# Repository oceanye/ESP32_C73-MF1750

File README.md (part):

# ESP32-S3 + E2802 Cascade eInk 调试工程

## 当前现场与开发状态（2026-08-08）

> 本节只作快速入口；任何后续变化、数量、测试批次和文件哈希均以
> [`docs/STATUS_HANDOFF.md`](docs/STATUS_HANDOFF.md) 为唯一事实源。

- 驱动板/J2 电源已关闭，ESP32 单独保持供电；当前未消费的可见刷新授权为 `0`，没有
  设备访问、刷写或面板动作在进行。
- RC2G 的 N0/N1 已放行真屏 action 为 `4/4`，均已闭环；对应 fixed claims 已永久消费，
  不得重跑。
- N2--N8 的 physical production-live 软件入口、深绑定、单次执行/finalizer/analyzer 均已落地，
  软件闭环为 `7/7`；对应旧 UNBOUND/self-sealed/legacy public live 入口在 claim/联网前
  fail closed。真屏阶段仍只有 N0/N1 完成；最终状态必须读取 STATUS。
- 各阶段的实际 process-policy/供应商限额、每 action 最新 usage/profile review、测量资产和授权
  尚未形成。软件入口
  就绪不等于硬件放行；reviewed limit/runtime、仪器、供应商数据、panel/build/
  prior 绑定和逐 action 授权等外部门禁仍阻断对应真屏任务；晚间顺序见
  [`docs/MF1750_N2_N8_EVENING_TASK_BOARD_2026-08-08.md`](docs/MF1750_N2_N8_EVENING_TASK_BOARD_2026-08-08.md)。

## 当前交接入口

- **唯一当前状态页（完成数、剩余数、目的、下一步）：[`docs/STATUS_HANDOFF.md`](docs/STATUS_HANDOFF.md)**
- **N2--N8 晚间逐项真屏任务板：[`docs/MF1750_N2_N8_EVENING_TASK_BOARD_2026-08-08.md`](docs/MF1750_N2_N8_EVENING_TASK_BOARD_2026-08-08.md)**
- 阶段一制造与固件交接：[`docs/STAGE1_REV_A1_HANDOFF_2026-07-13.md`](docs/STAGE1_REV_A1_HANDOFF_2026-07-13.md)
- 阶段二 ESP32/电池整合设计输入：[`docs/STAGE2_ESP32_BATTERY_INTEGRATION_BRIEF.md`](docs/STAGE2_ESP32_BATTERY_INTEGRATION_BRIEF.md)
- Rev B-mini ESP32/TF/电源与器件初评：[`docs/H1_REV_B_MINI_COMPONENT_ASSESSMENT_2026-08-05.md`](docs/H1_REV_B_MINI_COMPONENT_ASSESSMENT_2026-08-05.md)
- Rev B-mini L1/L2 小型化详细评估：[`docs/REV_B_MINI_L1_L2_DOWNSIZING_ASSESSMENT_2026-08-05.md`](docs/REV_B_MINI_L1_L2_DOWNSIZING_ASSESSMENT_2026-08-05.md)
- Rev A1 R16 级联整屏实测：[`docs/REV_A1_R16_CASCADE_FULLFRAME_TEST_2026-08-04.md`](docs/REV_A1_R16_CASCADE_FULLFRAME_TEST_2026-08-04.md)
- 基础驱动与 API 参考：[`docs/MF1750_DRIVER_API.md`](docs/MF1750_DRIVER_API.md)
- H0 Rev A1/RC2C 归档状态：[`docs/H0_REV_A1_RC2C_ARCHIVE_STATUS_2026-08-06.md`](docs/H0_REV_A1_RC2C_ARCHIVE_STATUS_2026-08-06.md)
- RC2F/C4/C2 分阶段上机任务包：[`docs/RC2F_C4_C2_HARDWARE_VALIDATION_TASKS_2026-08-06.md`](docs/RC2F_C4_C2_HARDWARE_VALIDATION_TASKS_2026-08-06.md)
- Spectra 6 色域映射高级 AI Handoff：[`docs/G1_SPECTRA6_GAMUT_MAPPING_HANDOFF_2026-08-05.md`](docs/G1_SPECTRA6_GAMUT_MAPPING_HANDOFF_2026-08-05.md)
- 重叠感知空间半色调研究：[`docs/S1_OVERLAP_AWARE_HALFTONE_RESEARCH_2026-08-06.md`](docs/S1_OVERLAP_AWARE_HALFTONE_RESEARCH_2026-08-06.md)
- G1/S1 混色与显示器模拟交接：[`docs/G1_S1_MONITOR_SIMULATION_HANDOFF_2026-08-06.md`](docs/G1_S1_MONITOR_SIMULATION_HANDOFF_2026-08-06.md)
- G1/S1 晚些真屏验证任务：[`docs/G1_S1_REAL_PANEL_VALIDATION_TASKS_2026-08-06.md`](docs/G1_S1_REAL_PANEL_VALIDATION_TASKS_2026-08-06.md)
- RC2G 白天开发与晚间逐项真屏 Campaign：[`docs/MF1750_RC2G_EVENING_HARDWARE_CAMPAIGN_2026-08-07.md`](docs/MF1750_RC2G_EVENING_HARDWARE_CAMPAIGN_2026-08-07.md)
- 网络照片与随机刷新 TODO：[`docs/TODO_NETWORK_RANDOM_PHOTO_PIPELINE.md`](docs/TODO_NETWORK_RANDOM_PHOTO_PIPELINE.md)
- 扩展颜色/亮度技术可行性结论：[`docs/EPD_EXTENDED_COLOR_FEASIBILITY_2026-08-05.md`](docs/EPD_EXTENDED_COLOR_FEASIBILITY_2026-08-05.md)
- 扩展颜色/亮度后续测试 TODO：[`docs/TODO_EPD_EXTENDED_COLOR_TESTS_2026-08-05.md`](docs/TODO_EPD_EXTENDED_COLOR_TESTS_2026-08-05.md)
- C3 转移感知优化器离线交接：[`docs/C3_TRANSITION_OPTIMIZER_OFFLINE_HANDOFF_2026-08-08.md`](docs/C3_TRANSITION_OPTIMIZER_OFFLINE_HANDOFF_2026-08-08.md)
- 扩展颜色远端成果集成审查：[`docs/EXTENDED_COLOR_INTEGRATION_REVIEW_2026-08-05.md`](docs/EXTENDED_COLOR_INTEGRATION_REVIEW_2026-08-05.md)
- 主机快速刷新、CI 与六色流水线总集成：[`docs/HOST_REFRESH_COLOR_INTEGRATION_2026-08-04.md`](docs/HOST_REFRESH_COLOR_INTEGRATION_2026-08-04.md)
- 多 AI TODO 与 Git 集成计划：[`docs/TODO_MULTI_AI_HANDOFF_PLAN_2026-08-04.md`](docs/TODO_MULTI_AI_HANDOFF_PLAN_2026-08-04.md)
- 新对话启动提示：[`docs/NEXT_SESSION_PROMPT.md`](docs/NEXT_SESSION_PROMPT.md)
- 1210 电容焊盘复核：[`docs/REV_A1_1210_PAD_AUDIT.md`](docs/REV_A1_1210_PAD_AUDIT.md)
- Rev A1 最终生产检查：[`hardware/mf1750_production_v1/production/FINAL_PREFLIGHT_revA1.md`](hardware/mf1750_production_v1/production/FINAL_PREFLIGHT_revA1.md)

当前状态：`MF1750 REV A1` 已完成加工与基础驱动 D0 实机验收。生产冻结文件
仍为带 `revA1_Q1FIX` 名称的 Gerber、BOM、CPL，禁止重新生成或覆盖。
H0 已生成基于 Git 对象的源码/证据归档和 SHA-256 清单，但精确验收二进制仍缺失，
且尚未完成异机持久副本；硬件验收 tag 未获明确授权，不能宣称 H0 已最终封版。

## 历史累计结论（起于 2026-08-04；不作为当前状态入口）

> 本节保留已经发生的硬件与软件证据，段内的“当前”“下一步”和回归计数只代表各自记录
> 时点；与顶部摘要或 STATUS 冲突时，一律以 STATUS 为准。

- 当前硬件为 R15 拆除、R16 0 Ω 安装、GPIO10 独立控制 `SL_CSB`。
- 两颗 SPD1657B 的 revision 均稳定读为 `0x04`。
- 向两颗控制器分别写 `CCSET(0xE0)=0x01` 后，左右半屏可独立显示纯色，
  并已实测完整 1024x600 连续六色色条。
- 从左到右白/黑/红/黄/蓝/绿正确，中央红/黄中缝清晰；正式分帧为每行
  512 字节，CS1 取前 256 字节、CS2 取后 256 字节。
- ESP32-S3 已由 esptool 与运行时共同确认约 8 MB OPI PSRAM；307200 字节
  规范帧的主机、设备生成器和非刷新 ingress 哈希均已通过。
- 当前源码候选固件为
  `MF1750_DRIVER_RC2G_R16_CCSET_MAPHASH_COLORGUARD_JOBTRACE_PSRFIX_WEBPHOTO_PHYSICAL_BUSYEDGE_2026-08-07`
  / driver API V3；它在 RC2F 上增加 PON/DRF/POF 命令前 idle、新 BUSY 边沿和
  safe-finish/final GPIO 证据。build 为 815664 字节、SHA-256 `9DF897…0CD772`，已于
  2026-08-07 精确刷入；MAP job1 与 macro4 job2 的协议、nominal timing、电气和
  frame fidelity 均通过。该 exact-action 范围不自动继承为其他算法资格。
  HTTP ingress 与公开驱动 API 都会在任何面板 I/O 前拒绝
  `0x4/0x7..0xF` 非法像素码；PON/DRF/POF 未观察到 BUSY 会 fail closed，
  POF 后的 PSR 寄存器写入保留等待证据但不要求额外 BUSY assertion；诊断报告
  以匹配的 operation ID 与产生它的 job/build 绑定。
- RC2C/V3 已用同一 MAP_ORIENT_V1 完成 100 kHz 协议复验和正式 1 MHz
  `/api/frame` 实屏验收；方向、中缝、颜色、完整/双 DTM 哈希、PON/DRF/POF
  BUSY、电源、温度及断电安全状态均正确。1 MHz 总耗时 34.187 秒，其中两半
  DTM 上传各 2.444 秒、DRF 约 21.7 秒。
- 主机 PSRAM 预检修正点 `2b19f75` 的 203 项回归、repository contract、
  PlatformIO build 与 GitHub CI run `30917129233` 全部通过；验收记录提交
  `fd548e3` 的 CI run `30918209821` 也通过。RC2C 实测 `firmware.bin` 为
  796272 字节、SHA-256 `F763FE…F45C475B`；RC2D 为 803120 字节、SHA-256
  `AE7427…943DAD`，
  在重新实屏验收前不得与 RC2C 的硬件证据混用。当前无 Rev A1 硬件 ECO 证据。
- 基础驱动 D0 已定版；普通图片与 Web UI 的软件合同已合入，但 calibrated palette
  真屏色彩、设备端认证、更高 SPI 扫频、快速波形和局刷仍是独立后续工作，不能
  由本次硬件通过自动提升状态。
- G1/S1 主机端显示器模拟基线已实现：严格 profile/hash、抖动前 tone/gamut
  mapping、三种 rendering intent、2×2/4×4 六色面积配方、真正的 void-and-cluster
  蓝噪声、六码面积 Bayer/蓝噪声、多色 DBS 和重叠感知多尺度 DBS，统一进入 10 算法、
  四阶段软预览页面。v2 artifact 固定为 `offline/formal=false`；没有 D65/2° 六色与
  混色色块实测、独立光学核及硬件 qualification 时，不得上传或声称真屏改善。
  独立受监督实验中，首个高负载 `area-weighted-ordered-8x8` 候选的精确帧与双 DTM
  hash 虽匹配，但 job2/op2 在 DRF 60010 ms 超时，POF cleanup 30005 ms 仍未闭环；
  用户实体断电，算法评价保持 `inconclusive`，授权永久消费。固定 MAP job3/op3
  随后以正常约 21.7 s DRF 恢复通过并再次断电。
- 低空间诊断 bundle 位于
  `.test-output/hardware/G1S1_LOW_SPATIAL_TRANSITION_MATCHED_20260806_231430/`；manifest
  原始文件 SHA-256 为 `07146b9254414e1454d9143f4af5706a8c5f69eb9125dce341206bbc441afb4d`，
  frame SHA-256/FNV-1a 为
  `ba373d138c525fd7e59cc6c4ae6037191fa41388507b347da9f6f8bdece9fc65` / `0xA9641618`，
  CS1/CS2 DTM FNV-1a 为
  `0xCB085C03` / `0x9ABD749A`。当时 J2-P1 已在持续监督会话中接通；non-displaying
  ingress 返回 `epd_action=none`、未刷新且 job 不变；随后
  attempt `38352ce6bc564530917c43099fe8d20a` 的 job4/op4 以
  PON/DRF/POF/post-PSR `181/21690/140/5 ms`、总时长 34169 ms 完成。用户确认真屏与
  `strict-final.png` 一致，3.3 V CV、电流、温度和 GPIO idle 正常；J2-P1 在继续受监督
  会话中保持接通。裁定仅为 `NOMINAL_DIAGNOSTIC_PASS`：全局终态直方图和全局 6×6
  转移计数各自都不是单独充分原因，空间频率与半屏负载仍未分离。row-major MAP-mask
  分配本来就不保留源图语义，画面难看不计画质；job2 仍为 `inconclusive`，根因未关闭，
  不产生任何算法 qualification。
- 后续 macro4 job5/op5 的 frame/双 DTM hash 与完整 sequence 精确匹配，但
  PON/DRF/total 为 `37110/39621/89049 ms`，明显偏离已知 nominal；用户确认画面与
  strict preview 一致，所以 `frame fidelity=PASS`，但主观画质差、4×4 块感明显。
  该次只能裁定 exact operation 成立、timing 异常、算法资格不成立；旧 claim 永久消费。
  证据裁决与 SHA 清单保存在
  `.test-output/hardware/G1S1_MACRO4_QUALITY_RUN1_20260807_004650/`。
- RC2G 已完成四次受控真屏 action：N0 的冷启动 MAP job1/op1 与 macro4 job2/op2，以及
  N1 的独立 MAP primer job1/op1 与 low-balanced job2/op2。四次的协议、frame/DTM hash、
  BUSY edge、安全 GPIO、电气和用户报告的 strict-preview 忠实度均通过；每个 fixed claim
  均已永久消费，禁止重跑。通用 runner 完成仍只代表单次协议和取证路径就绪；Q1--Q4
  自然图候选、四个独立 session 和八个 P0 action/claim declaration 已完成离线风险审计、
  深验证与冻结；physical-bound materializer、逐 action usage/profile 深绑定、one-shot/
  finalizer 与 tie-safe 四格总评器也已完成，但实际 policy 值、现场 panel/binding 文件、
  每 action approval 和授权均未形成，仍不能执行。旧 UNBOUND runner/claim 永久禁用。2×2 V2
  仍 `strict_metric_orthogonality_proven=false/upload_authorized=false`；N4 V3 已把五项预注册
  指标做到跨因素 exact 正交，固定 runner/finalizer/analyzer 也已完成，但 hardware/limit
  仍 blocked。N1 只提升 exact
  `low-balanced` action 为探索性 safety/fidelity PASS，不提升 bundle 或其他三格。
  RC2G MAP 为 `35006/180/22511/141/5 ms`，macro4 为
  `35017/181/22521/141/5 ms`（total/PON/DRF/POF/post-PSR）；macro4 忠实显示但
  主观画质差。旧时序异常未复现、根因未关闭。当前 J2-P1 已断开。
- N1 low-balanced 探索性 pilot 已闭环：primer result SHA-256 为
  `93d57feed9565344e20d10016977be8fc4754fbec09619316e96a8efed71f26a`；target result
  SHA-256 为 `0297015a4e6ad04a85435e7fe10cc3c75678be9811c76f82695da3d11ed37e0e`。
  用户确认目标真屏与 `low-balanced.strict-final.png` 一模一样、电气正常、ESP32 全程
  未重启，随后已物理断开 J2-P1。该图不评价自然图画质，也不放行 Q1--Q4。N2 四个
  自然图离线候选及 `MAP→候选` campaign 已于 2026-08-08 冻结。N2--N8 离线算法/计划
  包为 7/7；后来真实 preflight 重新打开 production live 深绑定修复。N2--N8 的
  physical production-live 软件链现均已闭环（`7/7`）。不能把软件完成写成硬件放行。
  真屏完成状态以 STATUS 为准。N6 已完成新的 physical operator CLI、N5 raw observation
  全量重算门、耐久 receipt/incident 边界和真实 Chromium physical E2E；这些软件完成项均不绕过 measured
  inputs、reviewed limits/runtime、仪器和逐 action 授权等外部门禁。C3 参数化转移感知
  优化器也已实现，但等待 N5 实测 profile 才能正式运行；仍没有新的可见刷新授权。
- N0/N1 阶段曾分别留下多批回归、repository contract、compileall、JavaScript syntax、
  diff check 与 PlatformIO build 通过记录。这些数字是历史快照，不是当前全仓最终计数；
  最新验证批次与哈希只看 STATUS。

## 2026-08-05 扩展颜色与亮度可行性结论

- 面板规格写明 `3-bit E6`，当前应用帧则是 4bpp packed 容器；4bpp 不代表存在
  16 个独立颜色。正式有效码仍只有 `0/1/2/3/5/6`。
- 若未来由用户逐阶段授权，第一轮最大范围仅限于原厂初始化和片上 OTP waveform
  不变的六色基线、恢复流程、`6×6` 转换矩阵，以及受控的小面积 `0x4/0x7`
  数字编码探针。
- 正式 `/api/frame` 继续拒绝 `0x4/0x7..0xF`。未来未知码只能通过默认关闭、
  固定图案、哈希锁定、一次性授权的隔离实验入口执行，不能放宽生产颜色校验。
- 当前 Rev A1 不是可编程 TCON：没有已知 LUT upload、内部 phase、局刷窗口、
  温度读取或独立高压控制接口。取得 SPD1657B rev `0x04`、当前 OTP 和厂商安全
  资料前，禁止猜寄存器、改 LUT/相位/高压或移植 SPD1656 命令。
- 当前没有软件可控 J2-1、PGOOD、板载电流/温度/高压联锁，因此未知码、耐久和
  waveform 实验均处于 `PENDING/BLOCKED`，等待用户逐阶段安排和授权。
- 远端 `research/extended-color-20260805` 的官方证据矩阵、测量记录合同、固定
  `0x4/0x7` 离线图、6×6 transition scaffold 和六码面积混色模拟已经完成本地集成
  审查；这些工具不含设备 I/O，仍固定为 `Hardware tested: NO`。合并不代表未知码、
  新颜色、恢复流程或真实混色色域已经通过实屏验证。

完整证据、公式修订、测量门禁和第一轮十个问题见扩色可行性文档；可执行任务、
依赖和停止条件见扩色测试 TODO。两份文档都不构成上电、COM8 刷写或刷新授权。

## 2026-08-05 Rev B-mini 第一轮架构结论

- H1 已记录 ESP32、TF、共用 3.3 V 与 L1/L2 小型化评估；原理图、PCB 和 BOM
  尚未冻结，也没有修改 Rev A1。
- 当前首选架构候选是 `ESP32-S3-WROOM-1-N8R8` 邮票孔射频模组，保留已验证
  的 8 MB Flash/8 MB OPI PSRAM；裸 SoC 不用于首版，XIAO ESP32-S3 Plus
  只作为快速工程样对照。若 WROOM 仍不能满足机械尺寸，再评估约 7×7 mm 的
  `ESP32-S3-PICO-1-N8R8` SiP，但它需要自研 RF/天线和 EMC 验证。
- 应用是低频刷新相框，当前不升级 ESP32-P4：高质量量化由现有浏览器或后续
  服务器 API 执行，S3 负责联网、TF 缓存、严格帧校验和刷新；本地基础量化只
  作为后备。P4 需额外网络协处理器，只有 S3 实测不达标才重开选型。
- TF 首版优先独立 SPI；当前电子纸驱动的双向 GPIO11 和断电片选状态使共享
  SPI 不是无条件接线替换。
- 产品架构建议由一颗有足够瞬态能力的 3.3 V 主稳压器分支供 ESP32、TF 和
  EPD，EPD 分支经过软件可控 load switch。当前 DevKit 3V3 → J2-1 只能另行
  授权做诊断，不是量产电源结论。
- L1/L2 第一轮以 15 µH 高性能 5030 为候选基线；4040 只作测流后的实验选项，
  器件与布局均未冻结。

## 构建与仓库边界

固件使用 PlatformIO。首次克隆后先复制 Wi-Fi 配置模板；真实凭据文件不会进入
Git：

```powershell
Copy-Item src\wifi_secrets.example.h src\wifi_secrets.h
platformio run
```

当前固件优先连接 `wifi_secrets.h` 配置的现有 Wi-Fi，并由路由器 DHCP 分配地址；
串口启动日志会打印 `WiFi STA IP`。只有 STA 在超时内连接失败时才回退到设备热点，
因此不要把历史示例中的 `192.168.4.1` 当成固定调试地址。

`hardware/mf1750_production_v1/production/` 内带 `revA1_Q1FIX` 名称的冻结生产
文件属于版本基线，禁止重新生成或覆盖。工作区可另外保留 EPDiy 与 Seeed Wiki
的第三方镜像、EDA 日志和调试截图；这些体积较大且可重新获取，已由 `.gitignore`
排除，不属于本项目的可交付源文件。

驱动 API 的输入边界是规范的 `1024x600`、4bpp 六色像素帧。完整字库、文字
排版、图像缩放、抖动和颜色量化属于后期渲染/应用层；不得耦合进
`epd_driver`。诊断层可以保留少量固定测试图元，但不承担通用字体渲染。

当前实验固件的 HTTP 控制接口没有应用层认证，只能放在可信、隔离的调试网络。纯软件、
离线生成和本地验证不要求切断 J2-1，但也不得因此访问设备；受监督硬件 run 成功到达
POF/safe-finish 且 GPIO idle 后，可在同一持续监督会话中保持上电，异常状态或监督会话
结束时必须实体断电，无人看管时同样保持 J2-1 断电。正式应用版必须增加 token/一次性
arm，或在 release 构建中关闭 legacy/危险诊断路由，不能把主机 CLI 的确认参数当成
设备端权限控制。

## 2026-07-13 可生产 PCB 状态

项目现在包含一块面向 MF-1750 / M009F-T（7.5 英寸、1024 x 600、
双 SPD1657）的完整级联驱动转接板 `MF1750 REV A1`：

- 生产目录：`hardware/mf1750_production_v1/production/`
- 嘉立创 PCB：`Gerber_mf1750_revA1_Q1FIX.zip`
- 嘉立创 SMT：`BOM_mf1750_revA1_Q1FIX.csv` +
  `CPL_mf1750_revA1_Q1FIX.csv`
- KiCad 源文件：`hardware/mf1750_production_v1/`
- 下单和首板检查：`production/PCB下单与首板检查.md`

这块板替代不兼容的 DESPI-C73 50pin 屏接口，并包含 MF-1750 A1 参考
电路所需的升压、负压和电荷泵网络。它不是 ESP32 主控板，也不含板载
3.3 V 稳压器；J2 需要外接 ESP32-S3 和稳定的 3.3 V 电源。

默认装配 R15，把 `CSB` 与 `SL_CSB` 相连，按 E2802 cascade 参考板的
单 CS 方式工作。需要独立第二片选时，先拆 R15，再装 R16，并将 J2-9
连接到 GPIO10；两者禁止同时安装。J2 前 8 脚沿用现有 DESPI-C73 顺序。

最终自动检查结果：ERC 0、DRC 0、未连接焊盘 0、原理图/PCB 一致性
错误 0。以上只能证明设计文件内部一致，首板仍必须核对屏尾 pin 1 与
接触面、嘉立创贴装方向，并在接屏前限流测量各高压电源轨。

Rev A1 已按器件数据手册修正 Q1 为 `1=G、2=S、3=D`，并把负压泵
D2 修正为 `K=GND、A=NEG_PUMP_H`；下单时只使用带 `revA1_Q1FIX`
名称的三个文件，避免与修正前上传记录混淆。

当前工程基于你提供的 `E6_73_sample code_V1.2_20250116` 和 `InkCubic_ E2802_cascade 电子纸E6转接板.pdf` 调整。

## 2026-06-10 验证记录（历史，已被 Rev A1/R16 结果取代）

> 本节及其后的 C73 接口排查是历史记录，用于解释为什么制作 Rev A1。
> 本段记录当时按 R15 共片选与 `EPD_PIN_CS2=-1` 排查的过程；当前首板已经
> 拆 R15、装 R16=0 Ω，并以 GPIO7/GPIO10 独立控制两颗 SPD1657B。不得把下述
> 旧 C73/R15 结论当成当前接线。

本轮软件/硬件联合测试结论：

- 当前 ESP32 + DESPI-C73 接线可以稳定驱动左半屏 `512x600`。
- `/api/bars-512x600` 测试结果：左侧通高显示完整 `白/黑/红/黄/蓝/绿` 六色条，说明当前 SPI、颜色编码、4bpp 像素格式、初始化和刷新流程对左半屏是正确的。
- `/api/bars-800x480` 测试结果：左侧显示 `白/黑/红/黄`，黄色略窄，底部出现通长肉色条。原因是 `800x480` 只覆盖 480 行，物理屏高为 600，底部 `120` 行未被刷新，保留残影/中间态。
- `/api/bars` 当前按 `1024x600` 发送 `307200` 字节，全屏会进入刷新流程，但最终仍主要只有左半屏出现渐变/残影，不能形成完整六色条。
- 3-wire 9-bit SPI 已测试，`PON/DRF/POF` 的 BUSY 立即返回，面板没有进入正常约 21 秒刷新流程；当前接线应继续使用 4-wire SPI + DC。
- 因此，“调整分辨率”只能解释并修正左半屏显示格式，不能在当前 DESPI-C73 硬件上单独解决右半屏不显示。

当前明确结论：

```text
整屏物理分辨率：1024 x 600
当前可驱动区域：左半屏 512 x 600
当前可用片选：CSB
缺失关键控制：SL_CSB / CS2
```

要实现完整 `1024x600`，仍需要把 MF-1750 pin 4 `SL_CSB` 引到 ESP32 的第二片选 GPIO，并在软件中分别向两颗控制器写入两个 `512x600` 半帧。现有 DESPI-C73 的 50pin pin 4 在图纸中不是 `SL_CSB`，不能直接当作第二片选使用。

关键结论：

- 当前面板整屏分辨率按你确认配置为 `1024x600`。
- `MF-1750..1).pdf` 的面板说明包含 `0.5T + SPD1657 * 2ea` 和 `7.50" TFT; 1024 X 600 DOTS`，因此这块屏本身就是双驱动/双半屏结构。
- `MF-1750` 的 50pin FPC 定义里，pin 4 是 `SL_CSB`，pin 31 是 `CSB`。当前只刷一半屏，最可能就是只驱动了 `CSB`，而 `SL_CSB` 没有被 MCU 控制。
- `DESPI-C73-SCH-20251014.pdf` 的 P2 8pin 只引出 `3V3/GND/SDI/SCLK/CS/D-C/RES/BUSY`，没有第二片选；它的 P1 50pin 里 pin 4 标为 `VDD`，不是 `SL_CSB`，因此不能把 DESPI-C73 的 P1 当作 MF-1750 的完全匹配接口。
- 参考资料里的级联转接板是 `E2802 cascade`，PDF 明确标注 `4-wire SPI(Default)`。
- E2802 转接板 PDF 的主接口能看到 `3V3/SDI/SCLK/CS/D/C/RES/BUSY`，原理图内部还能看到 `SL_CSB`、`BS0`、`BS1`；其中 `BS0/BS1` 被拉到 `VDD`，说明无需单独接 `BS`。
- 只显示长边一半不是屏幕坏，而是级联屏只驱动了其中一颗 E2802。
- 工程现在按两颗控制器处理：每颗 E2802 的 `TRES` 为 `512x600`，整屏为两个 `512x600` 半屏拼接。

## 图纸比对结论

`MF-1750` 屏的关键 FPC 引脚：

| Pin | Signal | 作用 |
| --- | --- | --- |
| 4 | `SL_CSB` | Slave chip select，第二片/级联片选 |
| 26 | `BS0` | 低电平为 4-wire SPI，高电平为 3-wire 9-bit SPI |
| 27 | `BS1` | 低电平参考 `BS0`，高电平为 standard/dual/quad 4-wire SPI |
| 28 | `RST_N` | 复位 |
| 29 | `BUSY_N` | 忙信号 |
| 30 | `DC` | Data/Command |
| 31 | `CSB` | 主片选 |
| 32 | `SCL` | SPI 时钟 |
| 33 | `SI0` | SPI 数据输入 |

`DESPI-C73` 的 P2 8pin 接口只适合单片选 SPI：

| P2 Pin | Signal |
| --- | --- |
| 1 | `3V3` |
| 2 | `GND` |
| 3 | `SDI` |
| 4 | `SCLK` |
| 5 | `CS` |
| 6 | `D/C` |
| 7 | `RES` |
| 8 | `BUSY` |

危险点：`DESPI-C73` 的 P1 pin 4 在图纸中接 `VDD`，而 `MF-1750` 的 pin 4 是 `SL_CSB`。如果直接把 ESP32 GPIO 接到这个点，GPIO 拉低时可能短接电源。要驱动全屏，必须使用真正把 `SL_CSB` 引出的 E2802 cascade 转接板焊盘/排针，或改板前先断开 `P1 pin 4 -> VDD` 的连接。

## 当前接线（Rev A1 / R16 双独立片选）

| Rev A1 J2 | 信号 | ESP32-S3 |
| ---: | --- | --- |
| 1 | `3V3` | 稳定 3.3 V；用于驱动板上/断电 |
| 2 | `GND` | `GND` |
| 3 | `SI0/MOSI` | `GPIO11` |
| 4 | `SCL/SCK` | `GPIO12` |
| 5 | `CSB` / CS1 | `GPIO7` |
| 6 | `DC` | `GPIO6` |
| 7 | `RST_N` | `GPIO5` |
| 8 | `BUSY_N` | `GPIO4` |
| 9 | `SL_CSB` / CS2 | `GPIO10` |
| 10 | `GND` | `GND` |

当前实板必须保持 R15 拆除、R16=0 Ω；R15 与 R16 禁止同时安装。FPC 禁止
带电插拔，所有逻辑信号均为 3.3 V。旧 C73、单 CS、R15 共片选和
`EPD_PIN_CS2=-1` 只属于前期排查记录，不能作为当前接线执行。

## 当前测试入口与边界

固件优先接入 `wifi_secrets.h` 配置的现有 Wi-Fi，实际 URL 以串口打印的
`WiFi STA IP` 为准；`192.168.4.1` 仅是 STA 失败后的 AP 回退地址，不是固定
调试地址。RC2C/V3 已完成 D0 正式验收；RC2F/V3 已完成受监督固定 MAP 基准、高负载
事故、固定 MAP 恢复、低空间诊断和 macro4 job5。RC2G/V3 已完成精确 MAP job1 与
macro4 job2 受监督验证；macro4 忠实度通过但画质差，旧时序异常根因未关闭。
当前现场为驱动板/J2 断电、ESP32 单独供电，且没有常驻可见刷新授权；晚间每个 exact action 都必须由用户当次授权并由独立 claim
永久消费。纯软件测试不要求改变 J2-P1 状态，但未经用户重新明确确认，不刷写 COM8、
不访问设备或任何会触发刷新的 HTTP 路由。晚间执行见
[`N2--N8 晚间逐项真屏任务板`](docs/MF1750_N2_N8_EVENING_TASK_BOARD_2026-08-08.md)。

RC2F 当前固件的设备首页提供照片工具模式：选择一次原图后，可在 Atkinson、
Floyd–Steinberg、无抖动和 8x8 有序抖动间切换，同时对比原图构图与实际六色
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
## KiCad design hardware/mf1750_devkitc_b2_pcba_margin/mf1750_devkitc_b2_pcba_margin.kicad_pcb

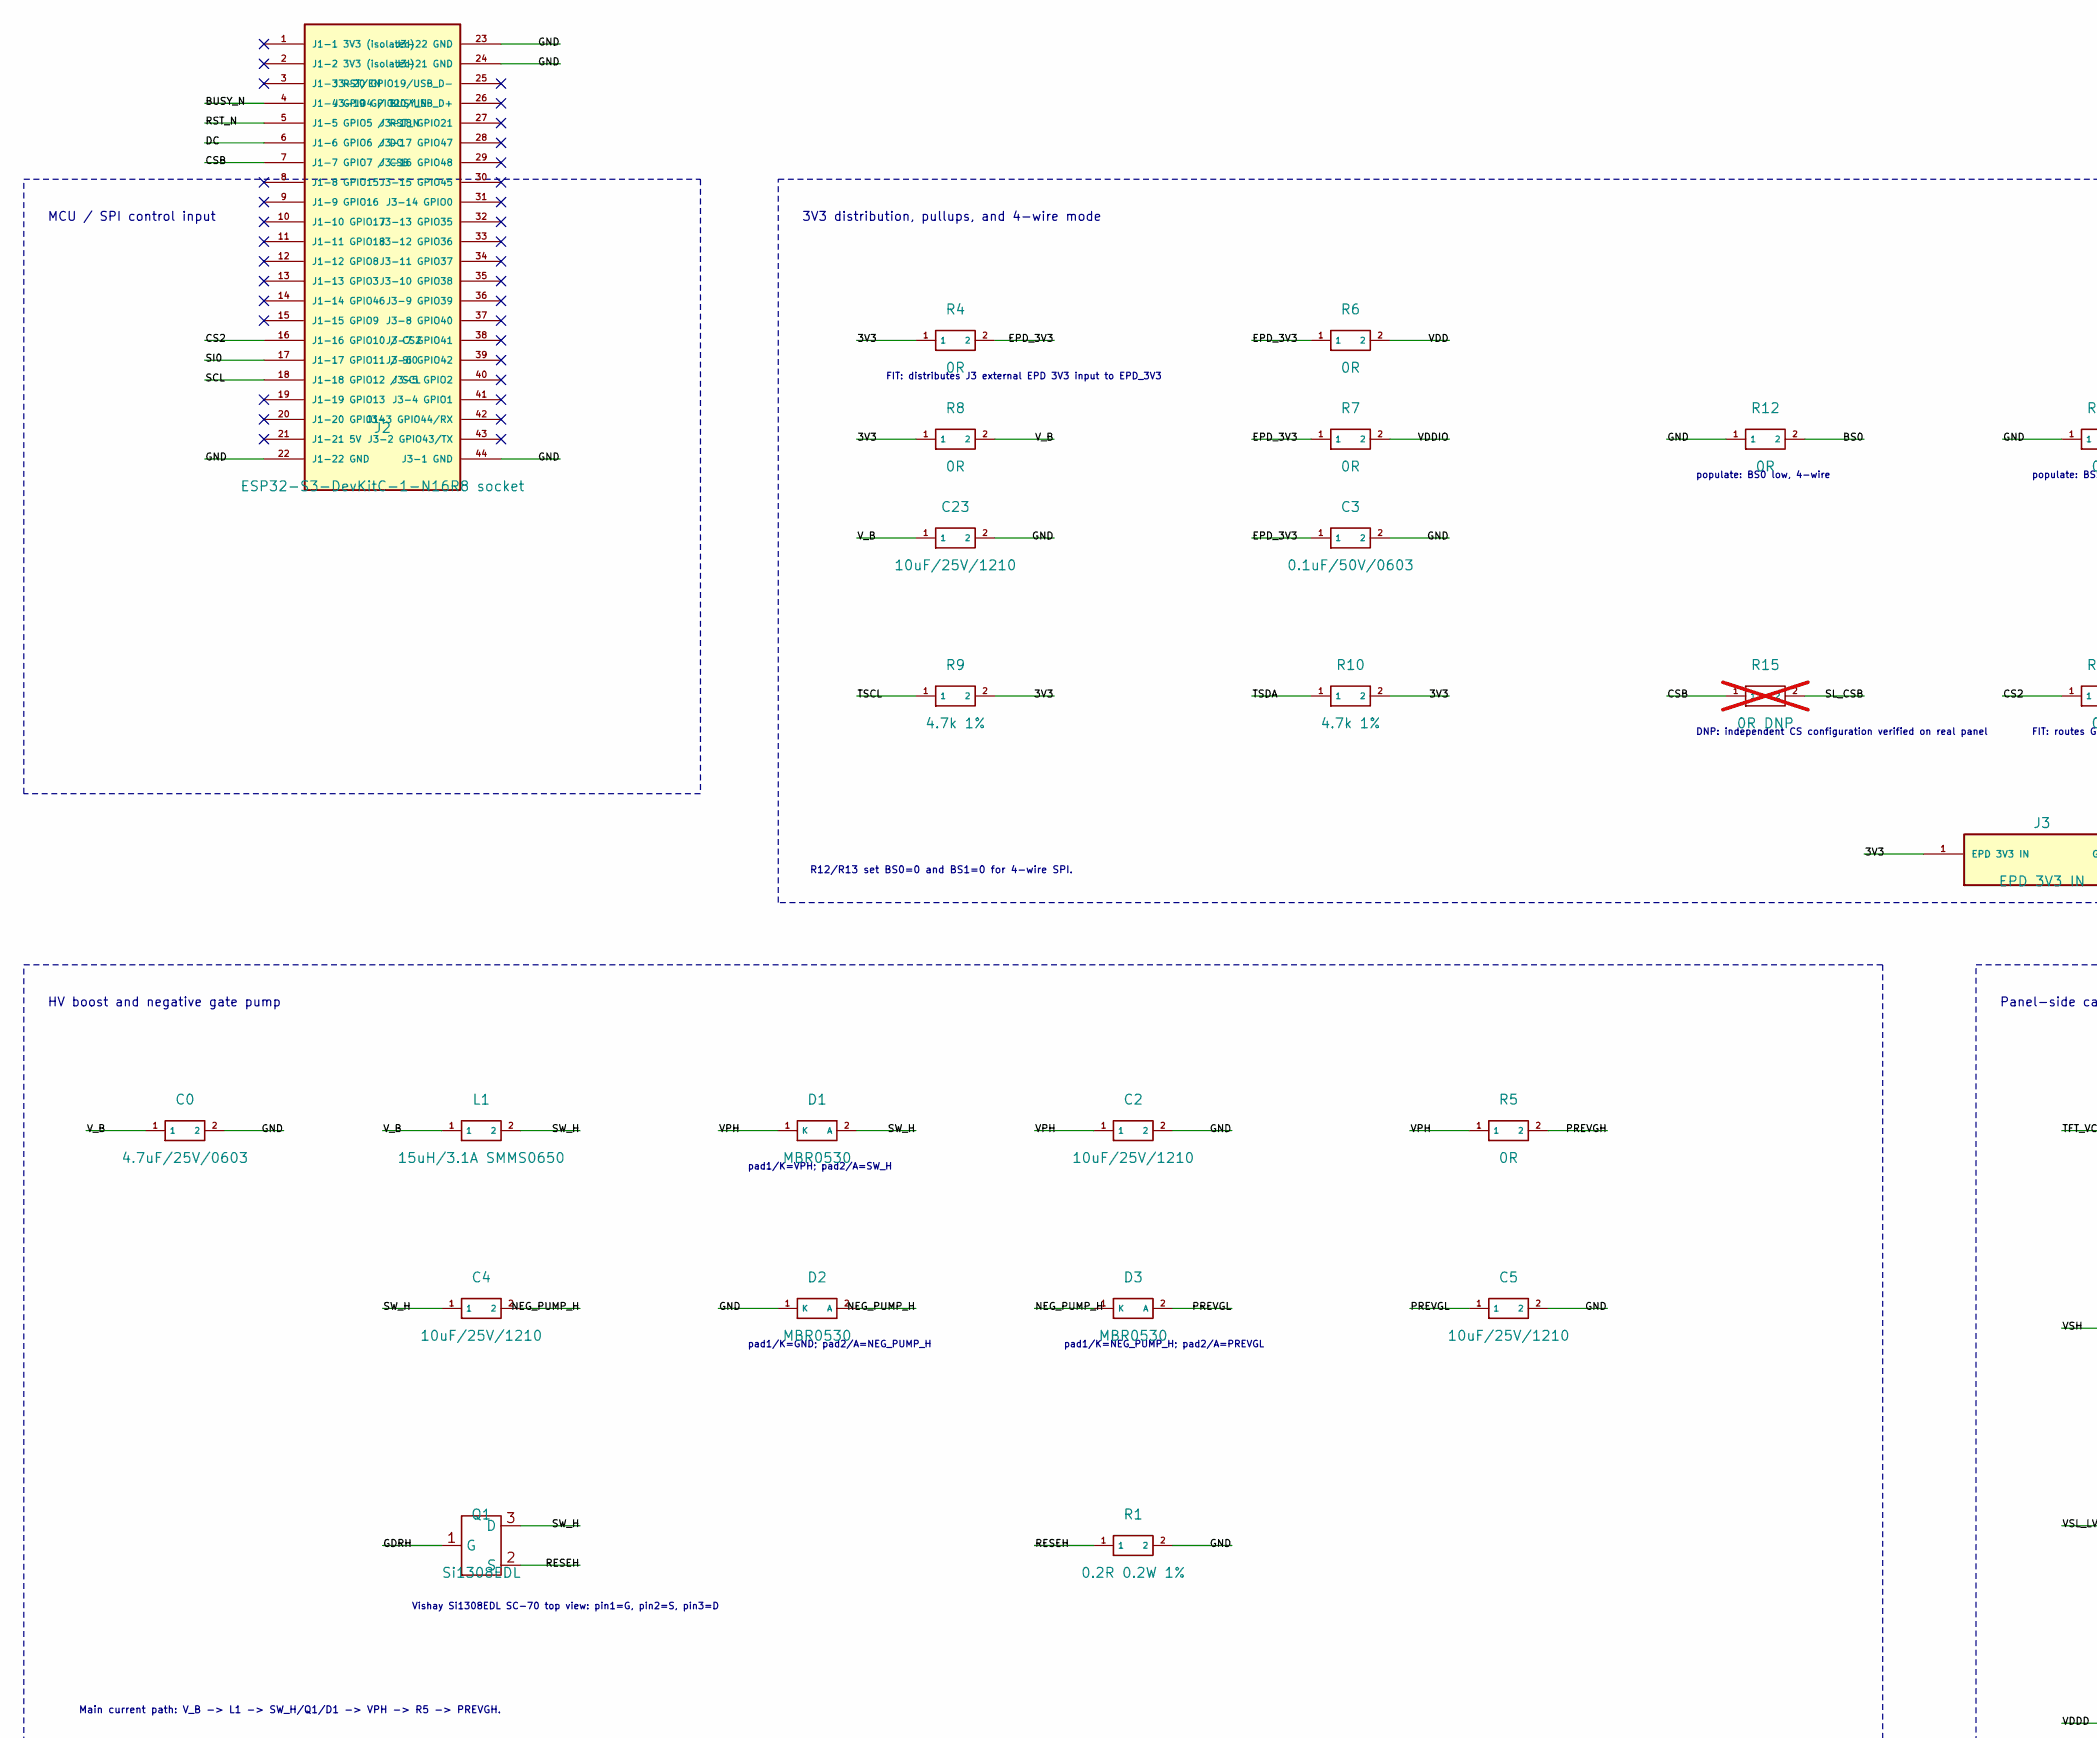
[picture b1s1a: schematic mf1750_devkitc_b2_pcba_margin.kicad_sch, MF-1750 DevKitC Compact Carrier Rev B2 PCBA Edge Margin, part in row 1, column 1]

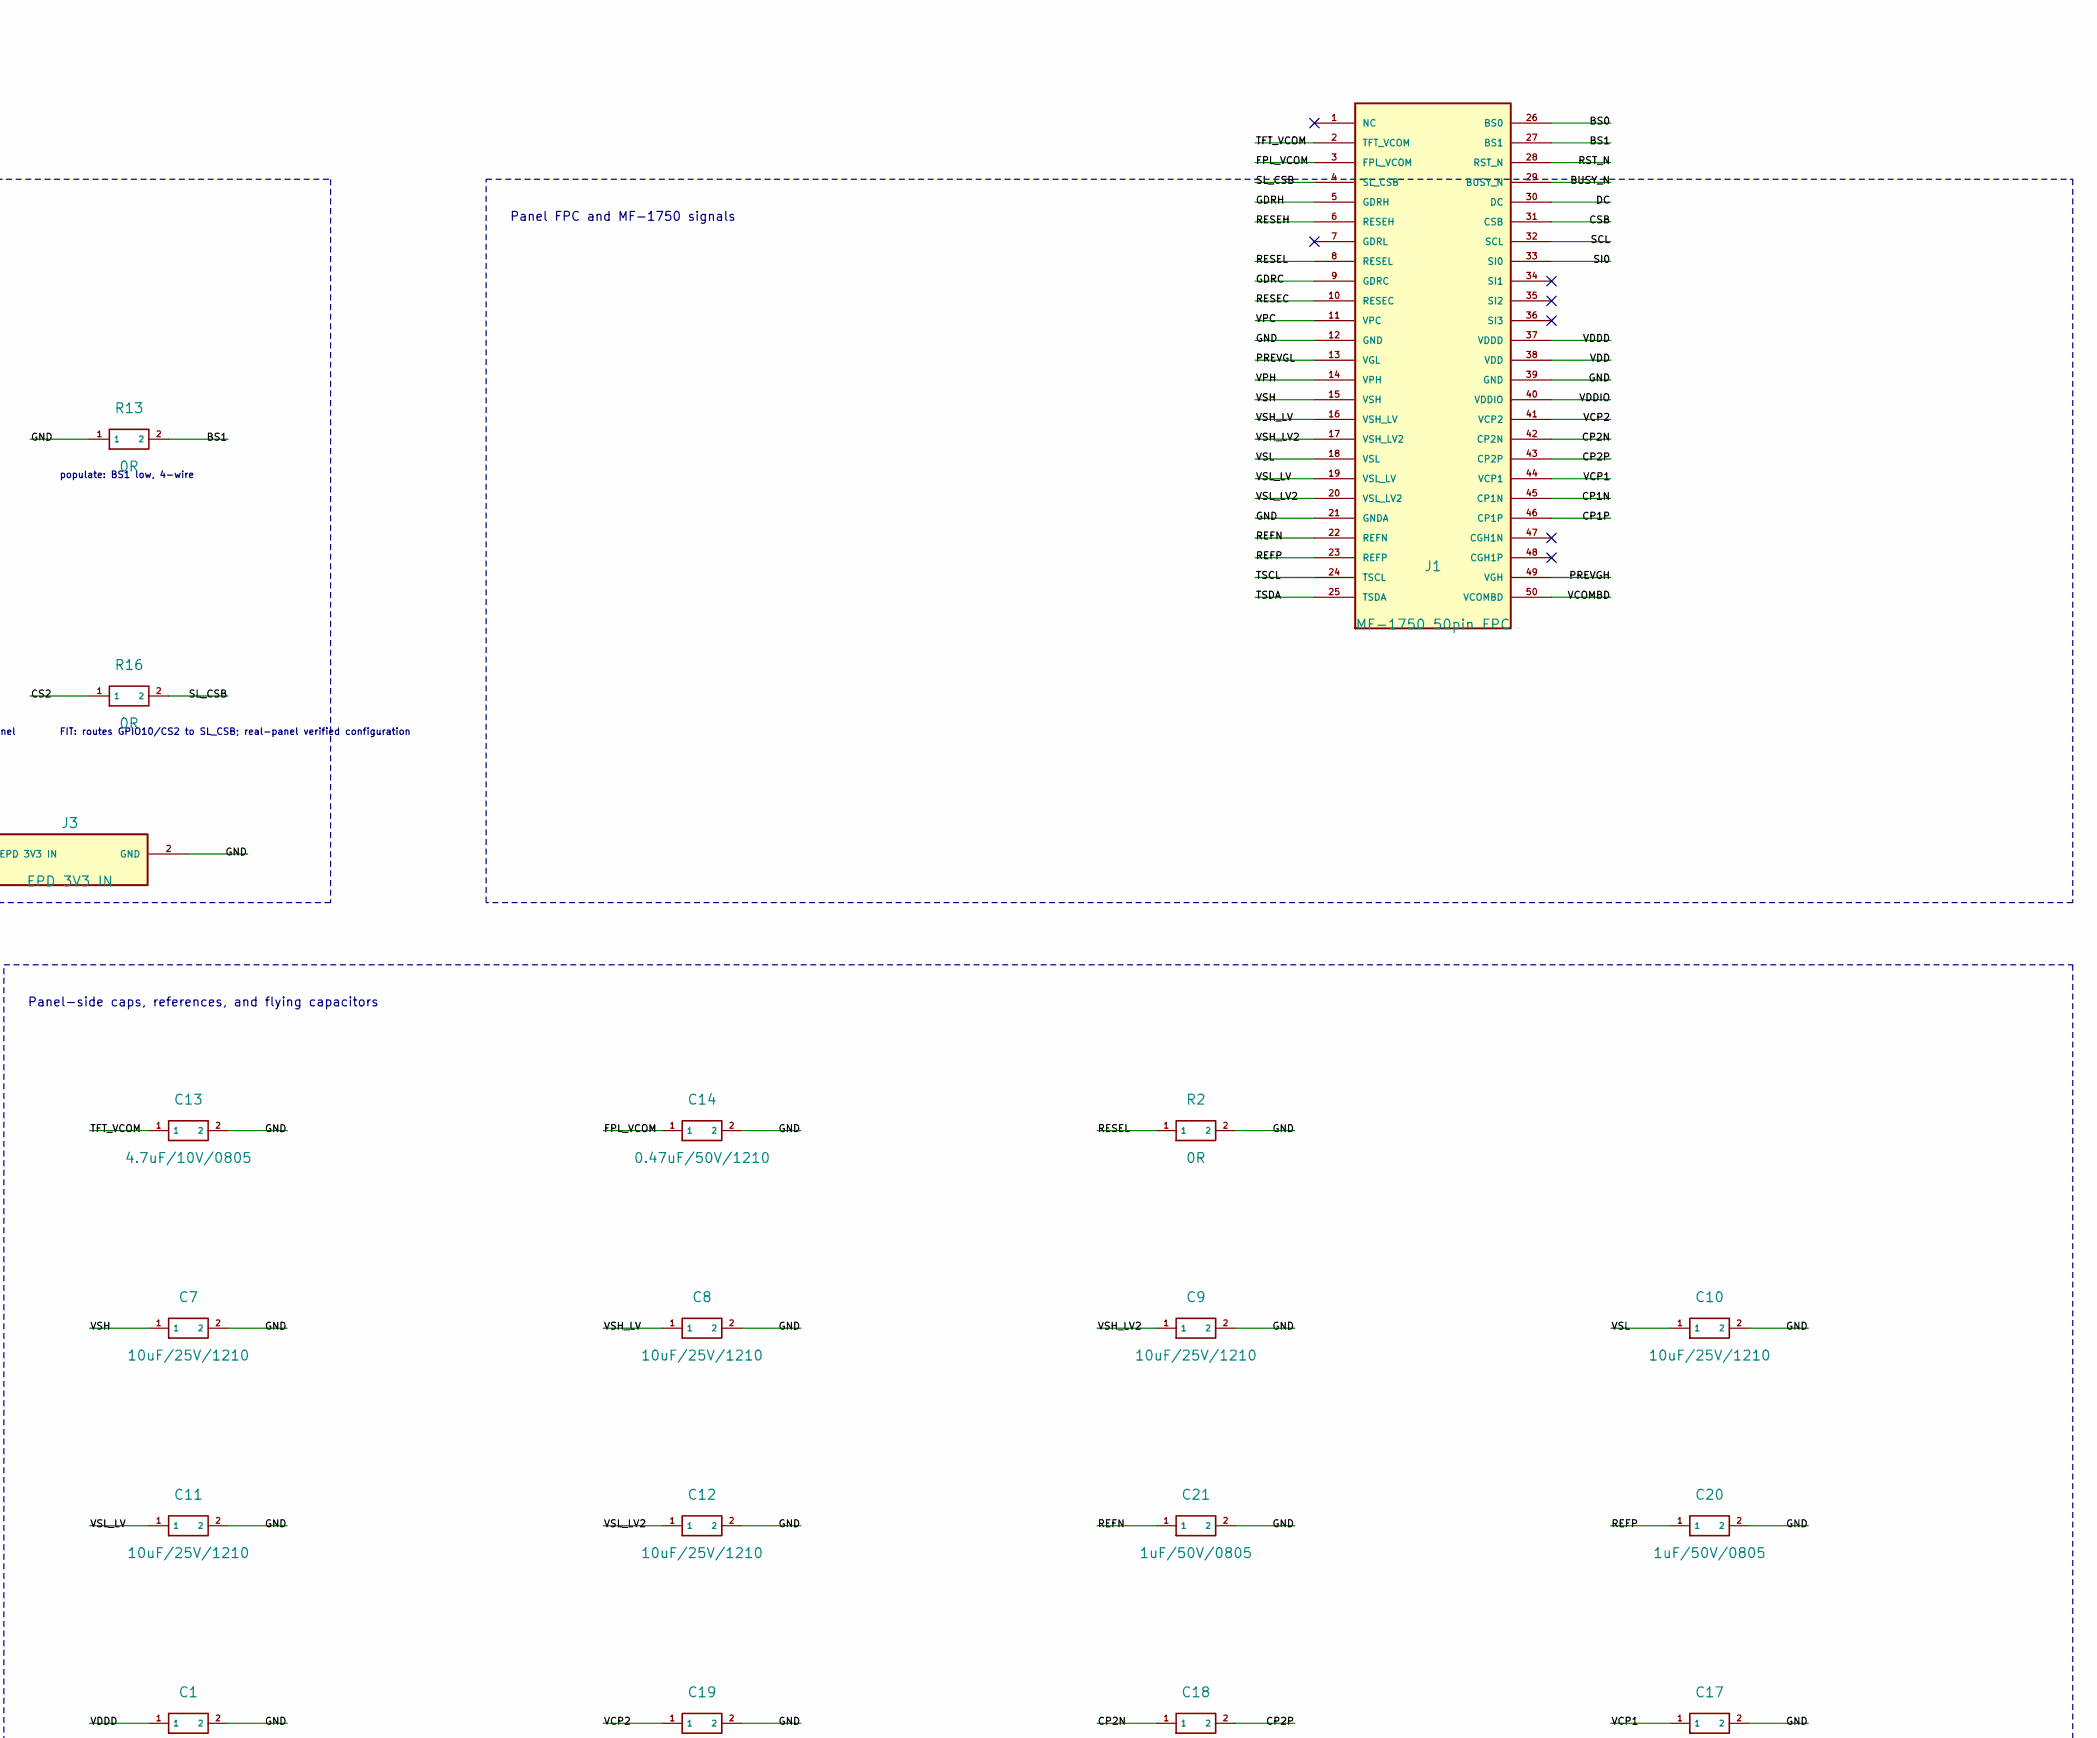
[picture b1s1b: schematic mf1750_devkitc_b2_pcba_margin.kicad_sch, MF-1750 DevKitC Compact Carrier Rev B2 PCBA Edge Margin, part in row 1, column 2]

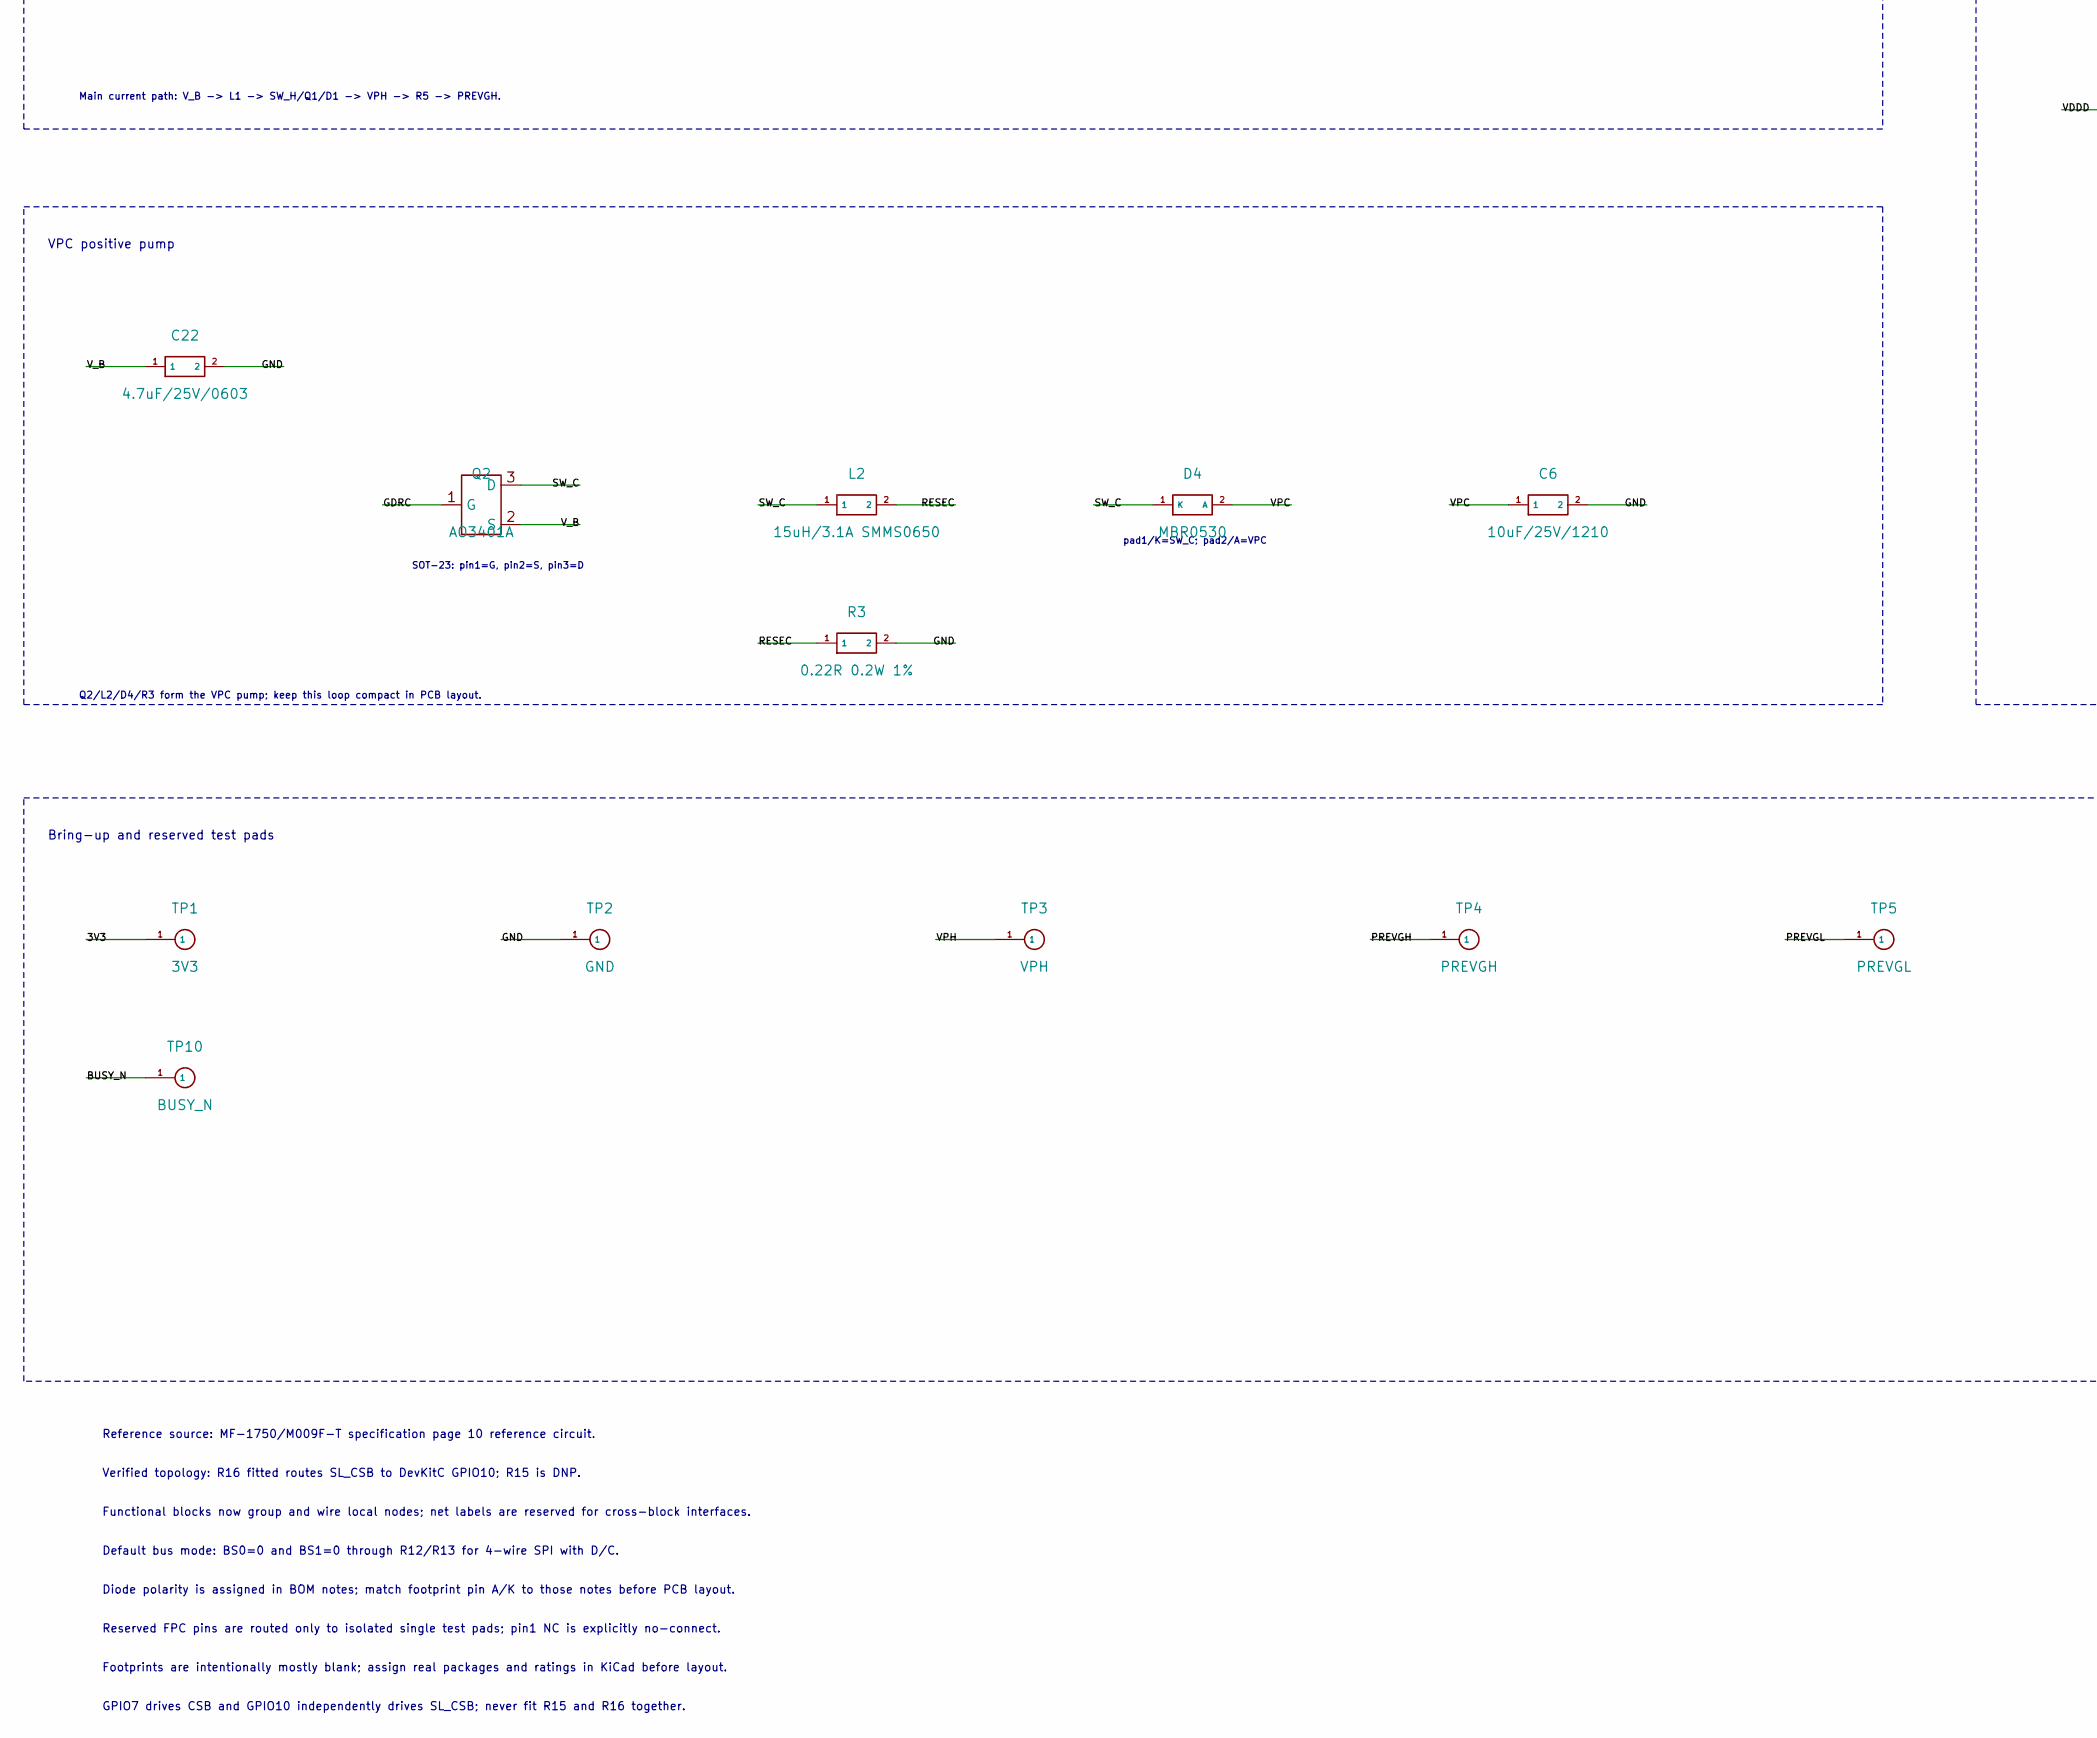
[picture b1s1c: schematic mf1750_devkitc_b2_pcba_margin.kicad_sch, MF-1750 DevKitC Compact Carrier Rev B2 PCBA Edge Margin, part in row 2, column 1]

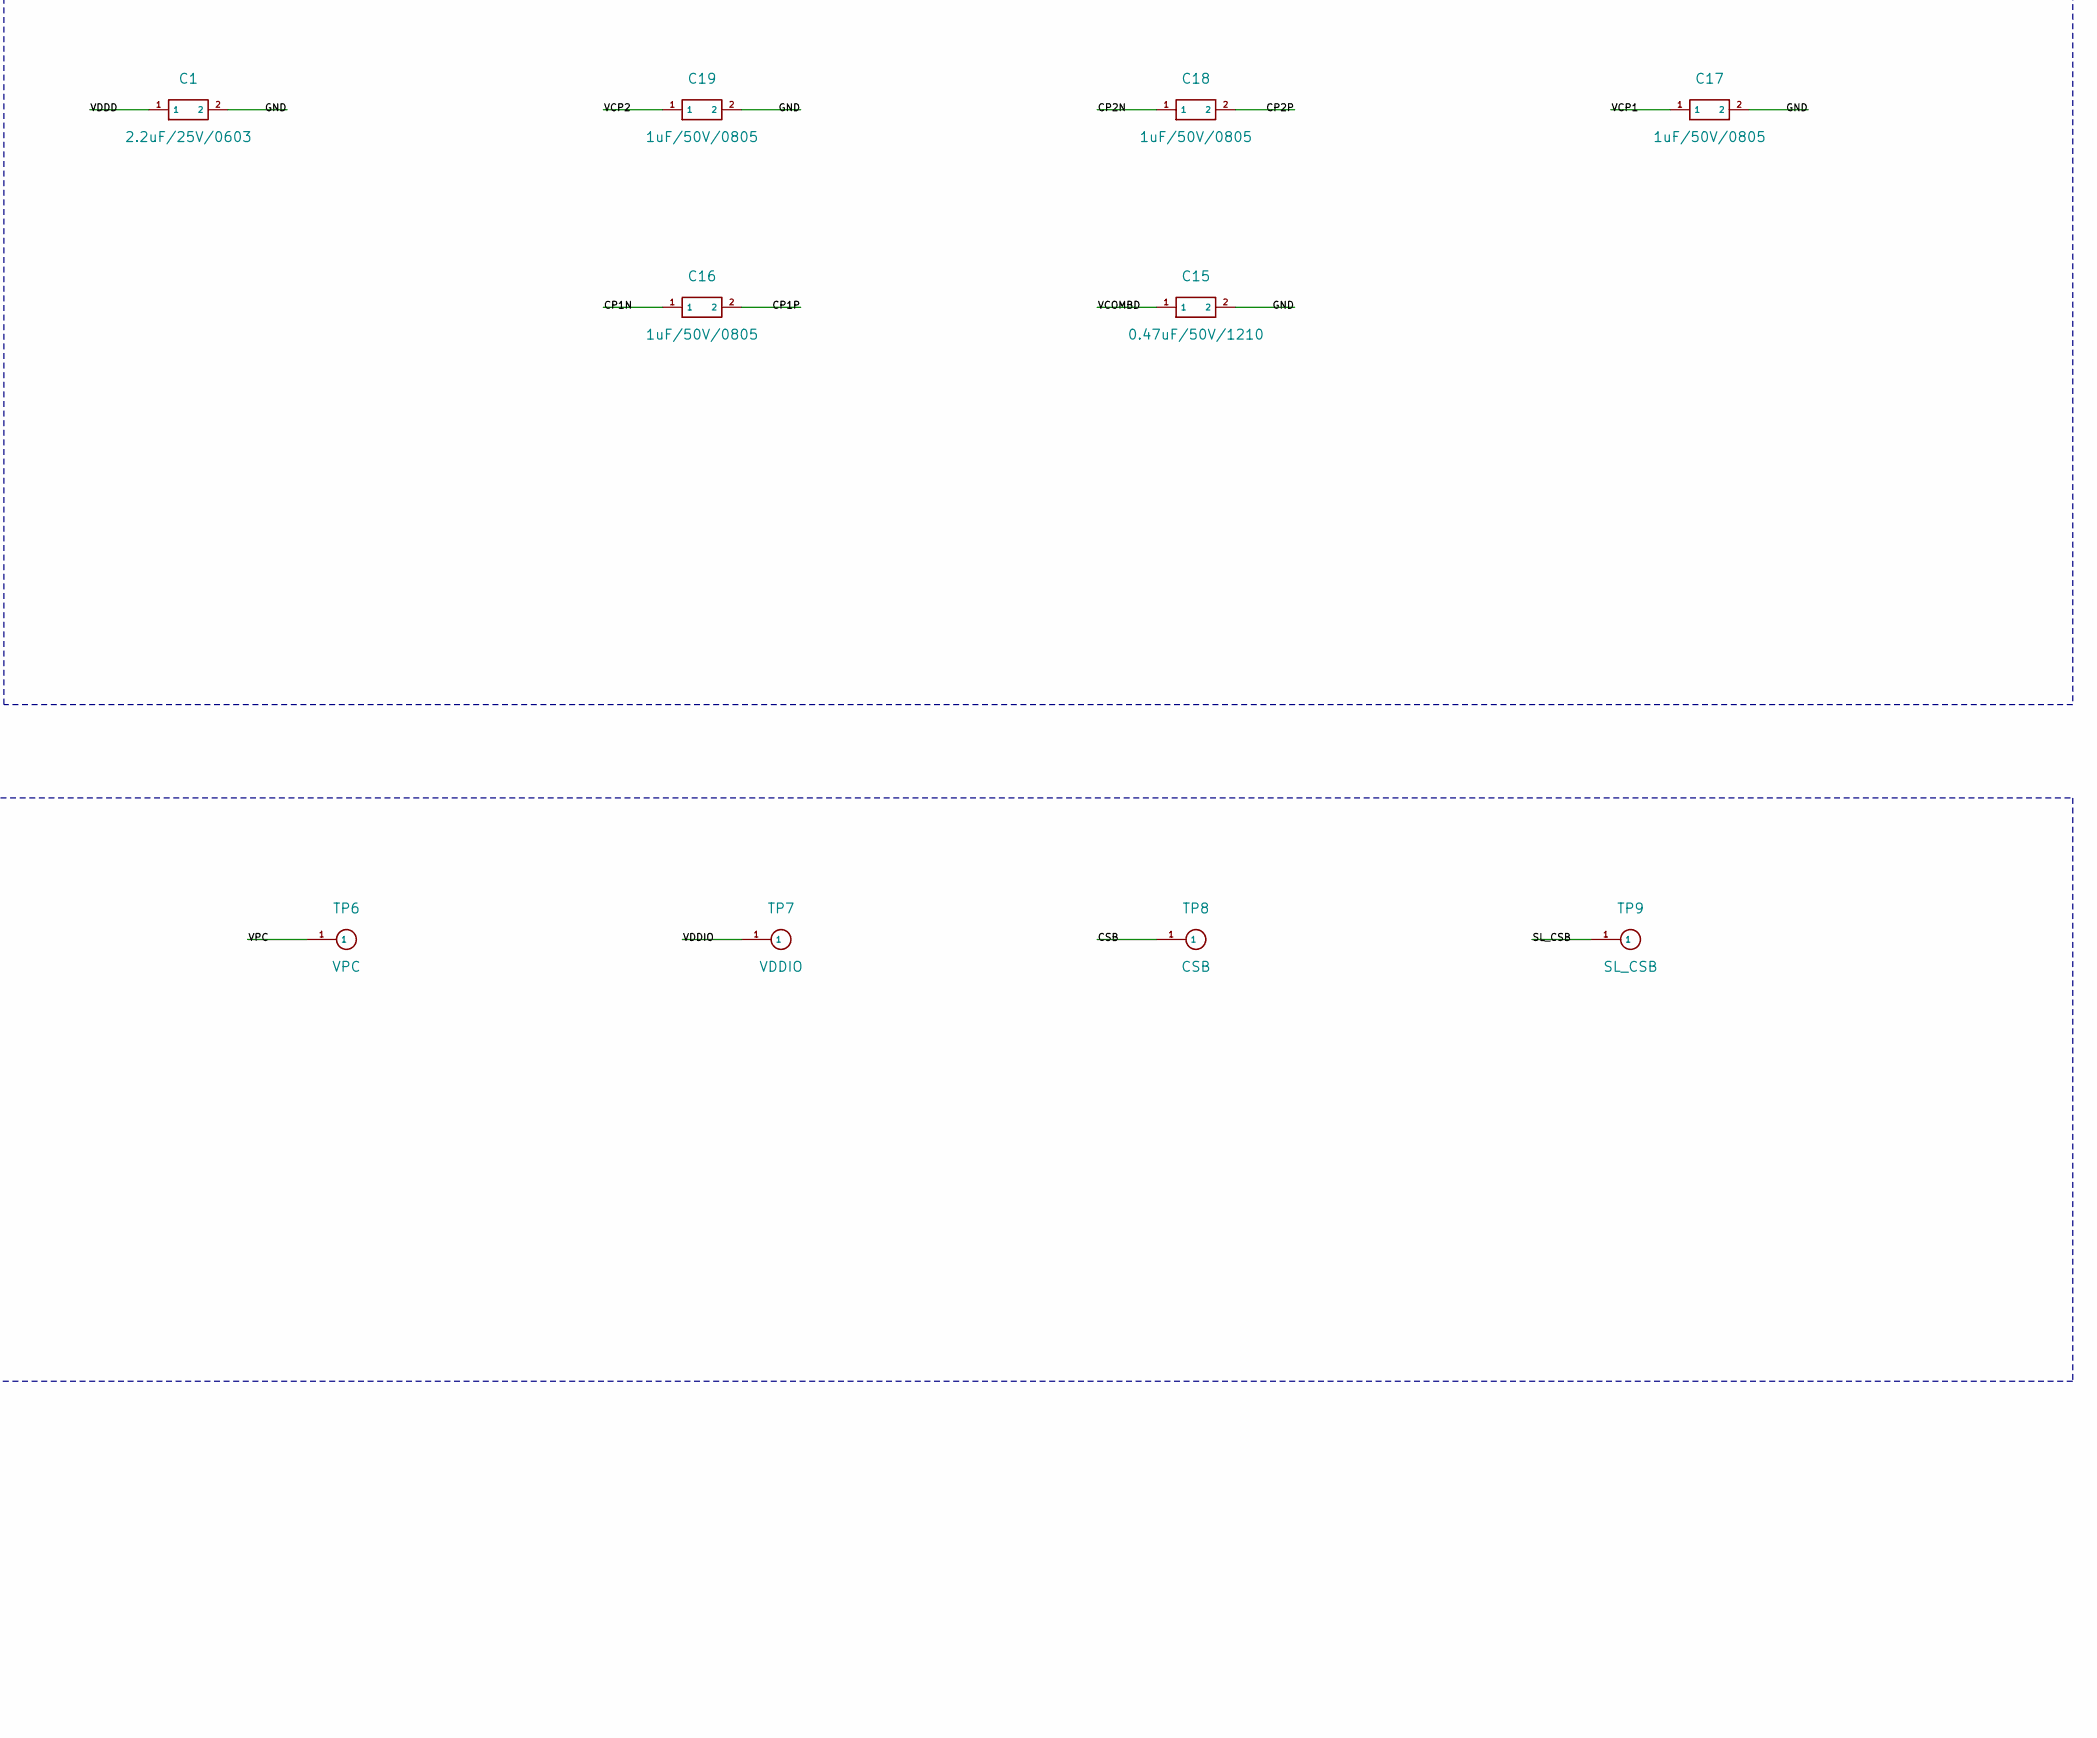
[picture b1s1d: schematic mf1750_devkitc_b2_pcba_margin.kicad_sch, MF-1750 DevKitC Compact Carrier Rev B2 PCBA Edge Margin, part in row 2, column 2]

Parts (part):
C0, C22: 4.7uF/25V/0603; C_0603_1608Metric
C1: 2.2uF/25V/0603; C_0603_1608Metric
C2, C4, C5, C6, C7, C8, C9, C10, C11, C12, C23: 10uF/25V/1210; C_1210_3225Metric
C3: 0.1uF/50V/0603; C_0603_1608Metric
C13: 4.7uF/10V/0805; C_0805_2012Metric
C14, C15: 0.47uF/50V/1210; C_1210_3225Metric
C16, C17, C18, C19, C20, C21: 1uF/50V/0805; C_0805_2012Metric
D1, D2, D3, D4: MBR0530; D_SOD-123
J1: MF-1750 50pin FPC; XUNPU_FPC-05FB-50PH20_1x50_P0.5mm_DualContact
J2: ESP32-S3-DevKitC-1-N16R8 socket; ESP32-S3-DevKitC-1_Socket
J3: EPD 3V3 IN; JST_PH_S2B-PH-K_1x02_P2.00mm_Horizontal
L1, L2: 15uH/3.1A SMMS0650; SXN_SMMS0650_7.1x6.6mm
Q1: Si1308EDL; SOT-323_SC-70
Q2: AO3401A; SOT-23-3
R1: 0.2R 0.2W 1%; R_1206_3216Metric
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
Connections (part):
/3V3: J3.1 (EPD 3V3 IN), R4.1, R8.1, R9.2, R10.2, TP1.1
/BS0: J1.26 (BS0), R12.2
/BS1: J1.27 (BS1), R13.2
/BUSY_N: J1.29 (BUSY_N), J2.4 (J1-4 GPIO4 / BUSY_N), TP10.1
/CP1N: C16.1, J1.45 (CP1N)
/CP1P: C16.2, J1.46 (CP1P)
/CP2N: C18.1, J1.42 (CP2N)
/CP2P: C18.2, J1.43 (CP2P)
/CS2: J2.16 (J1-16 GPIO10 / CS2), R16.1
/CSB: J1.31 (CSB), J2.7 (J1-7 GPIO7 / CSB), R15.1, TP8.1
/DC: J1.30 (DC), J2.6 (J1-6 GPIO6 / DC)
/EPD_3V3: C3.1, R4.2, R6.1, R7.1
/FPL_VCOM: C14.1, J1.3 (FPL_VCOM)
/GDRC: J1.9 (GDRC), Q2.1 (G)
/GDRH: J1.5 (GDRH), Q1.1 (G)
/GND: C0.2, C1.2, C2.2, C3.2, C5.2, C6.2, C7.2, C8.2, C9.2, C10.2, C11.2, C12.2, C13.2, C14.2, C15.2, C17.2, C19.2, C20.2, C21.2, C22.2, C23.2, D2.1 (K), J1.12 (GND), J1.21 (GNDA), J1.39 (GND), J2.22 (J1-22 GND), J2.23 (J3-22 GND), J2.24 (J3-21 GND), J2.44 (J3-1 GND), J3.2 (GND), R1.2, R2.2, R3.2, R12.1, R13.1, TP2.1
/NEG_PUMP_H: C4.2, D2.2 (A), D3.1 (K)
/PREVGH: J1.49 (VGH), R5.2, TP4.1
/PREVGL: C5.1, D3.2 (A), J1.13 (VGL), TP5.1
/REFN: C21.1, J1.22 (REFN)
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
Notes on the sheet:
MCU / SPI control input
3V3 distribution, pullups, and 4-wire mode
HV boost and negative gate pump
VPC positive pump
Panel FPC and MF-1750 signals
Panel-side caps, references, and flying capacitors
Bring-up and reserved test pads
FIT: distributes J3 external EPD 3V3 input to EPD_3V3
populate: BS0 low, 4-wire
populate: BS1 low, 4-wire
DNP: independent CS configuration verified on real panel
FIT: routes GPIO10/CS2 to SL_CSB; real-panel verified configuration
R12/R13 set BS0=0 and BS1=0 for 4-wire SPI.
pad1/K=VPH; pad2/A=SW_H
pad1/K=GND; pad2/A=NEG_PUMP_H
pad1/K=NEG_PUMP_H; pad2/A=PREVGL
Vishay Si1308EDL SC-70 top view: pin1=G, pin2=S, pin3=D
Main current path: V_B -> L1 -> SW_H/Q1/D1 -> VPH -> R5 -> PREVGH.
pad1/K=SW_C; pad2/A=VPC
SOT-23: pin1=G, pin2=S, pin3=D
Q2/L2/D4/R3 form the VPC pump; keep this loop compact in PCB layout.
Reference source: MF-1750/M009F-T specification page 10 reference circuit.
Verified topology: R16 fitted routes SL_CSB to DevKitC GPIO10; R15 is DNP.
Functional blocks now group and wire local nodes; net labels are reserved for cross-block interfaces.
Default bus mode: BS0=0 and BS1=0 through R12/R13 for 4-wire SPI with D/C.
Diode polarity is assigned in BOM notes; match footprint pin A/K to those notes before PCB layout.
Reserved FPC pins are routed only to isolated single test pads; pin1 NC is explicitly no-connect.
Footprints are intentionally mostly blank; assign real packages and ratings in KiCad before layout.
GPIO7 drives CSB and GPIO10 independently drives SL_CSB; never fit R15 and R16 together.
